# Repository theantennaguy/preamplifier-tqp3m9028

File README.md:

# preamplifier-tqp3m9028
This is a test board for the preamplifier TQP3M9028 from former Triquint now Qorvo. Pre-amplifier for frequencies between 500-4000MHz.

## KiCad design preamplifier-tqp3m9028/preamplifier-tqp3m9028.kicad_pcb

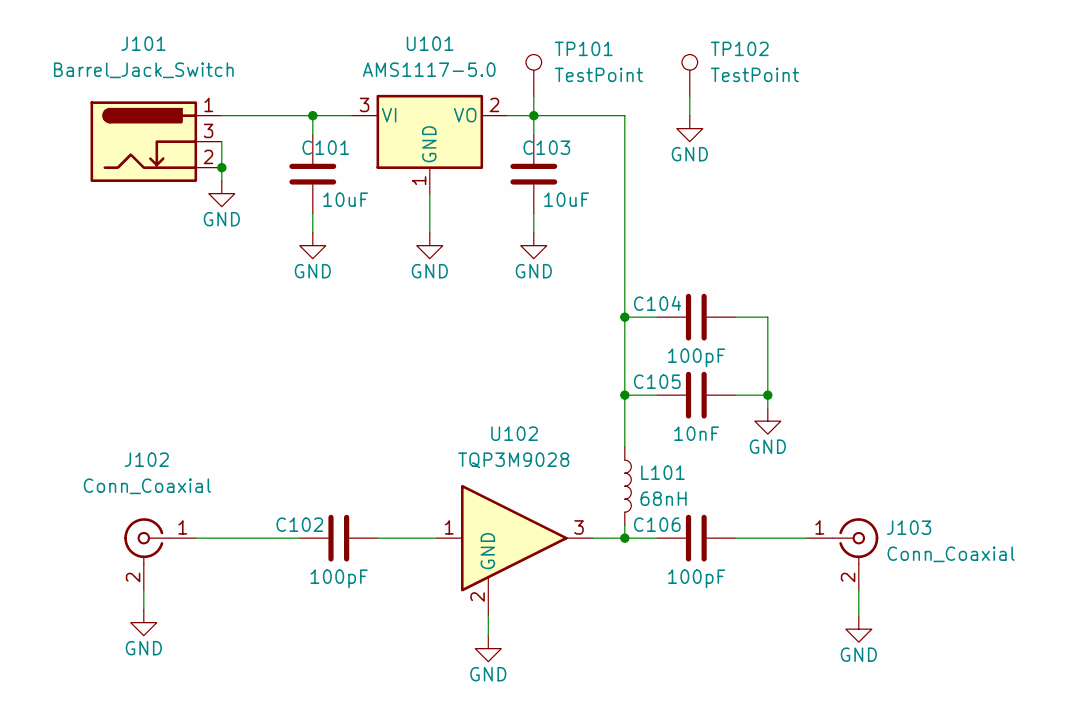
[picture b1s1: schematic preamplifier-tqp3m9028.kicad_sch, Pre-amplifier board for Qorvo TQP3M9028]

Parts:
C101, C103: 10uF; C_0805_2012Metric
C102, C104, C106: 100pF; C_0603_1608Metric
C105: 10nF; C_0603_1608Metric
J101: Barrel_Jack_Switch; BarrelJack_Wuerth_6941xx301002
J102, J103: Conn_Coaxial; LINX_CONSMA002-L
L101: 68nH; L_0603_1608Metric
TP101, TP102: TestPoint; TestPoint_Pad_D1.5mm
U101: AMS1117-5.0; SOT-223-3_TabPin2; Part Number AMS1117-5.0; LCSC C347223
U102: TQP3M9028; SOT-89-3

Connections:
GND: C101.2, C103.2, C104.2, C105.2, J101.2, J101.3, J102.2 (Ext), J103.2 (Ext), TP102.1, U101.1 (GND), U102.2 (GND)
unnamed: C101.1, J101.1, U101.3 (VI)
unnamed: C102.1, J102.1 (In)
unnamed: C102.2, U102.1
unnamed 4: C103.1, C104.1, C105.1, L101.1, TP101.1, U101.2 (VO); also elsewhere on the board
unnamed 5: C106.1, L101.2, U102.3; also elsewhere on the board
unnamed: C106.2, J103.1 (In)

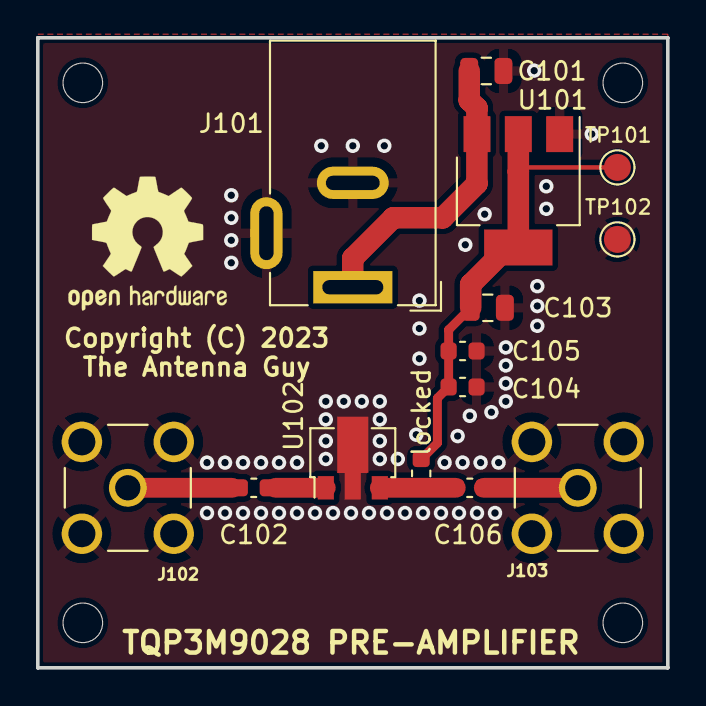
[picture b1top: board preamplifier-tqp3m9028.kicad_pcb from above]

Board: 2 copper layers, 35.0 x 35.0 mm, 18 parts (0 on the bottom side), 7 nets.

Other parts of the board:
 : MountingHole_2.2mm_M2_DIN965
 #2,  #3,  #4: MountingHole_2.2mm_M2_DIN965
locked: 68nH; L_0603_1608Metric

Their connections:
unnamed 4: locked.1; also elsewhere on the board
unnamed 5: locked.2; also elsewhere on the board

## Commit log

2022-12-18 Finished schematics - starts PCB
2022-12-27 Update PCB - relocate DC jack
2023-01-11 backups
2023-01-17 Finish PCB - generate fabrication files
2023-01-21 Update page layout

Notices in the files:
preamplifier-tqp3m9028/preamplifier-tqp3m9028.kicad_pcb:
Copyright (C) 2023
